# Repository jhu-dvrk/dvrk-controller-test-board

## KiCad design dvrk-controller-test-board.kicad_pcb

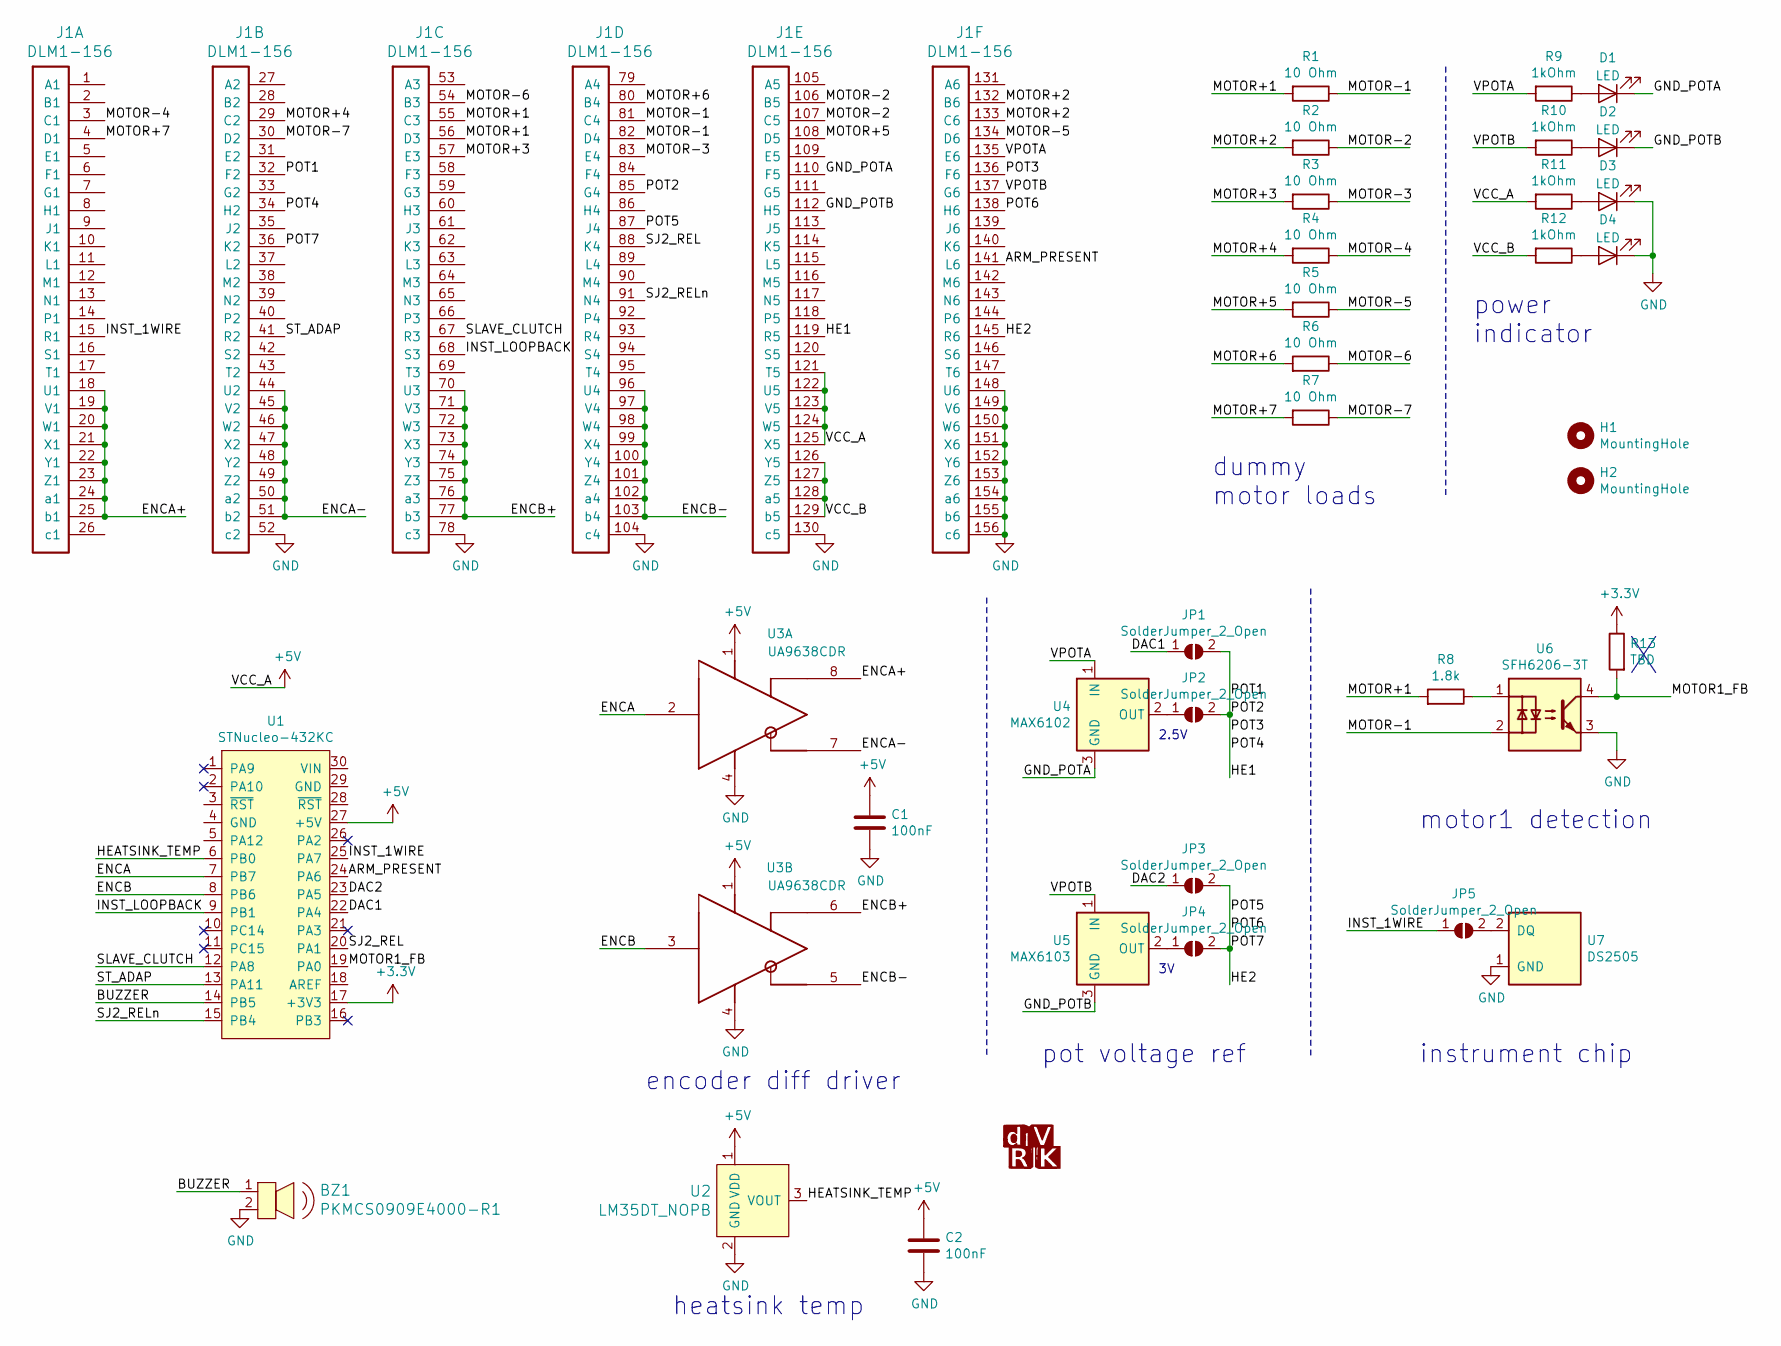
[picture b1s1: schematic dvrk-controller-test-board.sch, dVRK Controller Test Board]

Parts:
BZ1: PKMCS0909E4000-R1; Piezo_9x9mm_PKMCS0909E4000-R1; MPN PKMCS0909E4000-R1; Digi-Key_PN 490-9647-1-ND
C1, C2: 100nF; C_0402_1005Metric
D1, D2, D3, D4: LED; LED_0402_1005Metric
H1, H2: MountingHole; MountingHole_3.2mm_M3
J1: DLM1-156; DLM1-Plug
JP1, JP2, JP3, JP4, JP5: SolderJumper_2_Open; SolderJumper-2_P1.3mm_Open_TrianglePad1.0x1.5mm
R1, R2, R3, R4, R5, R6, R7: 10 Ohm; TO-220-2_Vertical
R8: 1.8k; R_0402_1005Metric
R9, R10, R11, R12: 1kOhm; R_0402_1005Metric
R13: TBD; R_0402_1005Metric
U1: STNucleo-432KC; STNucleo32
U2: LM35DT_NOPB; TO-220-3_Vertical; MPN LM35DT/NOPB; Digi-Key_PN LM35DT/NOPB-ND
U3: UA9638CDR; SOIC-8_3.9x4.9mm_P1.27mm
U4: MAX6102; SOT-23
U5: MAX6103; SOT-23
U6: SFH6206-3T; SMDIP-4_W9.53mm_Clearance8mm
U7: DS2505; TSOC-6

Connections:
+3V3: R13.1, U1.17 (+3V3)
+5V: C1.1, C2.1, J1.121 (T5), J1.122 (U5), J1.123 (V5), J1.124 (W5), J1.125 (X5), R11.2, U1.27 (+5V), U2.1 (VDD), U3.1 (VCC)
/ARM_PRESENT: J1.141 (L6), U1.24 (PA6)
/BUZZER: BZ1.1, U1.14 (PB5)
/DAC1: JP1.1 (A), U1.22 (PA4)
/DAC2: JP3.1 (A), U1.23 (PA5)
/ENCA: U1.7 (PB7), U3.2 (IN)
/ENCA+: J1.18 (U1), J1.19 (V1), J1.20 (W1), J1.21 (X1), J1.22 (Y1), J1.23 (Z1), J1.24 (a1), J1.25 (b1), U3.8 (OUTB)
/ENCA-: J1.44 (U2), J1.45 (V2), J1.46 (W2), J1.47 (X2), J1.48 (Y2), J1.49 (Z2), J1.50 (a2), J1.51 (b2), U3.7 (OUTA)
/ENCB: U1.8 (PB6), U3.3 (IN)
/ENCB+: J1.70 (U3), J1.71 (V3), J1.72 (W3), J1.73 (X3), J1.74 (Y3), J1.75 (Z3), J1.76 (a3), J1.77 (b3), U3.6 (OUTB)
/ENCB-: J1.96 (U4), J1.97 (V4), J1.98 (W4), J1.99 (X4), J1.100 (Y4), J1.101 (Z4), J1.102 (a4), J1.103 (b4), U3.5 (OUTA)
/GND_POTA: D1.1 (K), J1.110 (F5), U4.3 (GND)
/GND_POTB: D2.1 (K), J1.112 (H5), U5.3 (GND)
/HE1: J1.32 (F2), J1.34 (H2), J1.85 (G4), J1.119 (R5), J1.136 (F6), JP1.2 (B), JP2.2 (B)
/HE2: J1.36 (K2), J1.87 (J4), J1.138 (H6), J1.145 (R6), JP3.2 (B), JP4.2 (B)
/HEATSINK_TEMP: U1.6 (PB0), U2.3 (VOUT)
/INST_1WIRE: J1.15 (R1), JP5.1 (A), U1.25 (PA7)
/INST_LOOPBACK: J1.68 (S3), U1.9 (PB1)
/MOTOR1_FB: R13.2, U1.19 (PA0), U6.4
/MOTOR+1: J1.55 (C3), J1.56 (D3), R1.2, R8.2
/MOTOR+2: J1.132 (B6), J1.133 (C6), R2.2
/MOTOR+3: J1.57 (E3), R3.2
/MOTOR+4: J1.29 (C2), R4.2
/MOTOR+5: J1.108 (D5), R5.2
/MOTOR+6: J1.80 (B4), R6.2
/MOTOR+7: J1.4 (D1), R7.2
/MOTOR-1: J1.81 (C4), J1.82 (D4), R1.1, U6.2
/MOTOR-2: J1.106 (B5), J1.107 (C5), R2.1
/MOTOR-3: J1.83 (E4), R3.1
/MOTOR-4: J1.3 (C1), R4.1
/MOTOR-5: J1.134 (D6), R5.1
/MOTOR-6: J1.54 (B3), R6.1
/MOTOR-7: J1.30 (D2), R7.1
/SJ2_REL: J1.88 (K4), U1.20 (PA1)
/SJ2_RELn: J1.91 (N4), U1.15 (PB4)
/SLAVE_CLUTCH: J1.67 (R3), U1.12 (PA8)
/ST_ADAP: J1.41 (R2), U1.13 (PA11)
/VCC_B: J1.126 (Y5), J1.127 (Z5), J1.128 (a5), J1.129 (b5), R12.2
/VPOTA: J1.135 (E6), R9.2, U4.1 (IN)
/VPOTB: J1.137 (G6), R10.2, U5.1 (IN)
GND: BZ1.2, C1.2, C2.2, D3.1 (K), D4.1 (K), J1.52 (c2), J1.78 (c3), J1.104 (c4), J1.130 (c5), J1.148 (U6), J1.149 (V6), J1.150 (W6), J1.151 (X6), J1.152 (Y6), J1.153 (Z6), J1.154 (a6), J1.155 (b6), J1.156 (c6), U2.2 (GND), U3.4 (GND), U6.3, U7.1 (GND)
unnamed: D1.2 (A), R9.1
unnamed: D2.2 (A), R10.1
unnamed: D3.2 (A), R11.1
unnamed: D4.2 (A), R12.1
unnamed: JP2.1 (A), U4.2 (OUT)
unnamed: JP4.1 (A), U5.2 (OUT)
unnamed: JP5.2 (B), U7.2 (DQ)
unnamed: R8.1, U6.1

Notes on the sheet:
dummy motor loads
power indicator
pot voltage ref
motor1 detection
instrument chip
encoder diff driver
heatsink temp
2.5V

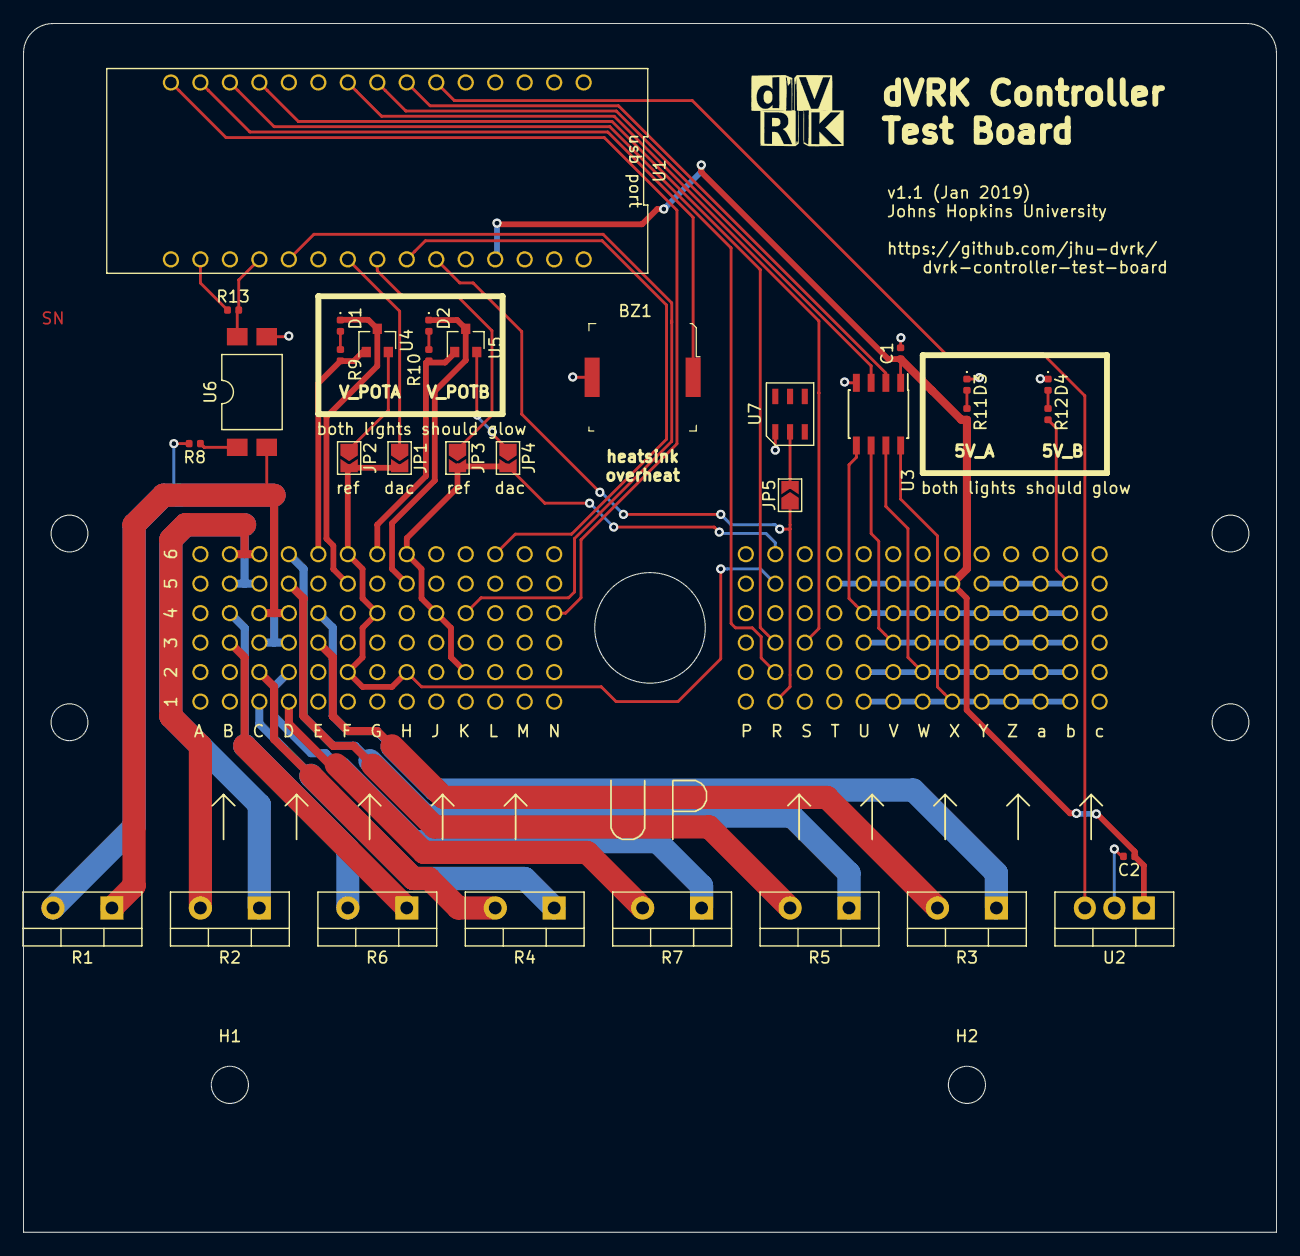
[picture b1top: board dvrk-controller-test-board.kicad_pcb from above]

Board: 2 copper layers, 107.9 x 104.1 mm, 35 parts (1 on the bottom side), 50 nets.

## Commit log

2019-01-03 created footprint for dlm1
2019-01-04 more schematic
2019-01-05 routing done. drc pass
2019-01-05 added logo
2019-01-05 reannotate
2019-01-05 clean up
2019-01-07 v1.1 address Peter's comments
